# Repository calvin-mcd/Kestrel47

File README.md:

# Kestrel47

collaboration with Falconloft\#4615

40s keyboard inspired by the TG4x. sandwich style case with midlayers case. Supports Bluetooth enabled micro controllers with use of this [power button](https://tech.alpsalpine.com/e/products/detail/SSSS811101/) as well as smd and throughhole style diodes.

Firmware for standard atmega & rp2040 pro micro style controllers is included. Bluetooth is supported for bluemicro style controllers.

concept, case design and firmware by Falconloft\#4615, pcb design by Calvin\#0563

## Layout

[Link](http://www.keyboard-layout-editor.com/#/gists/43b69fae42faf7c21a81fad3a4cf8861)

## Pictures

## Firmware

Firmware for both Atmega and rp2040 controllers is functional and included.

The Bluetooth firmware is zmk based, functional and included.

## Disclaimer

This PCB has been fully tested and confirmed to work. The members of the PCB development team are however not liable if you end up with a non-functional pcb. Order at your own risk. Support will not be provided but pull requests will be reviewed and possibly accepted.

## License

Shield: 

This work is licensed under a  
[Creative Commons Attribution-NonCommercial-ShareAlike 4.0 International License](http://creativecommons.org/licenses/by-nc-sa/4.0/).

## Credits

Any questions, contact Falconloft\#4615 & Calvin\#0563 on Discord.

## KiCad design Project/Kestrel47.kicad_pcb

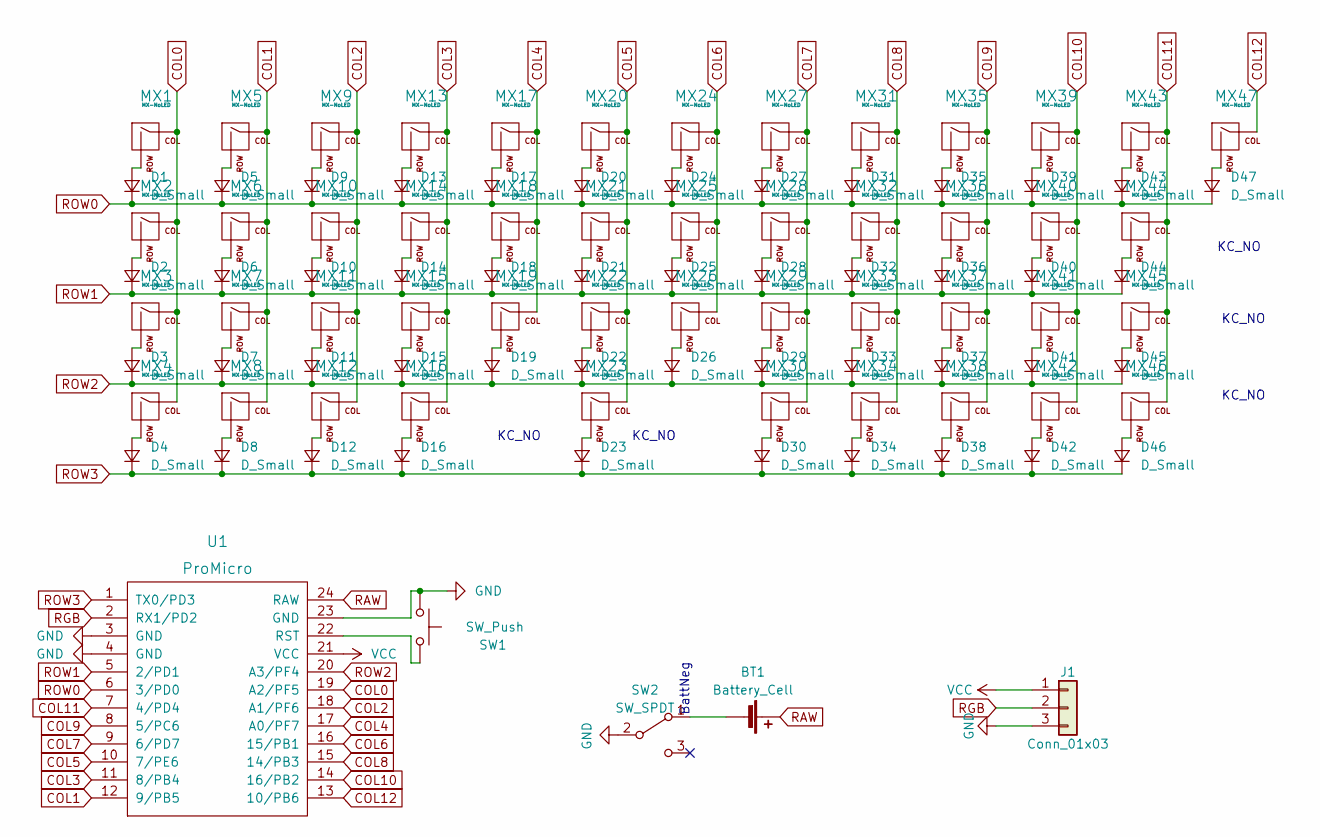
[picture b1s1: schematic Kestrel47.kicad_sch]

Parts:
BT1: Battery_Cell; cell_pads
D1, D2, D3, D4, D5, D6, D7, D8, D9, D10, D11, D12, D13, D14, D15, D16, D17, D18, D19, D20, D21, D22, D23, D24, D25, D26, D27, D28, D29, D30, D31, D32, D33, D34, D35, D36, D37, D38, D39, D40, D41, D42, D43, D44, D45, D46, D47: D_Small; ComboDiode
J1: Conn_01x03; PinSocket_1x03_P2.00mm_Vertical
MX1, MX5, MX6, MX7, MX8, MX9, MX10, MX11, MX12, MX13, MX14, MX15, MX17, MX18, MX19, MX20, MX21, MX22, MX23, MX24, MX25, MX26, MX27, MX28, MX29, MX31, MX32, MX33, MX34, MX35, MX36, MX37, MX38, MX39, MX40, MX41, MX42, MX43, MX47: MX-NoLED; MXOnly-1U-NoLED
MX2, MX46: MX-NoLED; MXOnly-1.25U-NoLED
MX3, MX45: MX-NoLED; MXOnly-1.5U-NoLED
MX4, MX44: MX-NoLED; MXOnly-1.75U-NoLED
MX16, MX30: MX-NoLED; MXOnly-2U-ReversedStabilizers-NoLED
SW1: SW_Push; PinHeader_1x02_P2.54mm_Vertical
SW2: SW_SPDT; switch_SSSS811101
U1: ProMicro; ArduinoProMicro

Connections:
ROW3: D4.1 (K), D8.1 (K), D12.1 (K), D16.1 (K), D23.1 (K), D30.1 (K), D34.1 (K), D38.1 (K), D42.1 (K), D46.1 (K), U1.1 (TX0/PD3)
COL0: MX1.1 (COL), MX2.1 (COL), MX3.1 (COL), MX4.1 (COL), U1.19 (A2/PF5)
COL1: MX5.1 (COL), MX6.1 (COL), MX7.1 (COL), MX8.1 (COL), U1.12 (9/PB5)
COL2: MX9.1 (COL), MX10.1 (COL), MX11.1 (COL), MX12.1 (COL), U1.18 (A1/PF6)
COL3: MX13.1 (COL), MX14.1 (COL), MX15.1 (COL), MX16.1 (COL), U1.11 (8/PB4)
COL4: MX17.1 (COL), MX18.1 (COL), MX19.1 (COL), U1.17 (A0/PF7)
COL5: MX20.1 (COL), MX21.1 (COL), MX22.1 (COL), MX23.1 (COL), U1.10 (7/PE6)
COL6: MX24.1 (COL), MX25.1 (COL), MX26.1 (COL), U1.16 (15/PB1)
COL7: MX27.1 (COL), MX28.1 (COL), MX29.1 (COL), MX30.1 (COL), U1.9 (6/PD7)
COL8: MX31.1 (COL), MX32.1 (COL), MX33.1 (COL), MX34.1 (COL), U1.15 (14/PB3)
COL9: MX35.1 (COL), MX36.1 (COL), MX37.1 (COL), MX38.1 (COL), U1.8 (5/PC6)
COL10: MX39.1 (COL), MX40.1 (COL), MX41.1 (COL), MX42.1 (COL), U1.14 (16/PB2)
COL11: MX43.1 (COL), MX44.1 (COL), MX45.1 (COL), MX46.1 (COL), U1.7 (4/PD4)
COL12: MX47.1 (COL), U1.13 (10/PB6)
GND: J1.3, SW1.1, SW2.2 (B), U1.3 (GND), U1.4 (GND), U1.23 (GND)
unnamed: BT1.2 (-), SW2.1 (A)
unnamed: D1.2 (A), MX1.2 (ROW)
unnamed: D2.2 (A), MX2.2 (ROW)
unnamed: D3.2 (A), MX3.2 (ROW)
unnamed: D4.2 (A), MX4.2 (ROW)
unnamed: D5.2 (A), MX5.2 (ROW)
unnamed: D6.2 (A), MX6.2 (ROW)
unnamed: D7.2 (A), MX7.2 (ROW)
unnamed: D8.2 (A), MX8.2 (ROW)
unnamed: D9.2 (A), MX9.2 (ROW)
unnamed: D10.2 (A), MX10.2 (ROW)
unnamed: D11.2 (A), MX11.2 (ROW)
unnamed: D12.2 (A), MX12.2 (ROW)
unnamed: D13.2 (A), MX13.2 (ROW)
unnamed: D14.2 (A), MX14.2 (ROW)
unnamed: D15.2 (A), MX15.2 (ROW)
unnamed: D16.2 (A), MX16.2 (ROW)
unnamed: D17.2 (A), MX17.2 (ROW)
unnamed: D18.2 (A), MX18.2 (ROW)
unnamed: D19.2 (A), MX19.2 (ROW)
unnamed: D20.2 (A), MX20.2 (ROW)
unnamed: D21.2 (A), MX21.2 (ROW)
unnamed: D22.2 (A), MX22.2 (ROW)
unnamed: D23.2 (A), MX23.2 (ROW)
unnamed: D24.2 (A), MX24.2 (ROW)
unnamed: D25.2 (A), MX25.2 (ROW)
unnamed: D26.2 (A), MX26.2 (ROW)
unnamed: D27.2 (A), MX27.2 (ROW)
unnamed: D28.2 (A), MX28.2 (ROW)
unnamed: D29.2 (A), MX29.2 (ROW)
unnamed: D30.2 (A), MX30.2 (ROW)
unnamed: D31.2 (A), MX31.2 (ROW)
unnamed: D32.2 (A), MX32.2 (ROW)
unnamed: D33.2 (A), MX33.2 (ROW)
unnamed: D34.2 (A), MX34.2 (ROW)
unnamed: D35.2 (A), MX35.2 (ROW)
unnamed: D36.2 (A), MX36.2 (ROW)
unnamed: D37.2 (A), MX37.2 (ROW)
unnamed: D38.2 (A), MX38.2 (ROW)
unnamed: D39.2 (A), MX39.2 (ROW)
unnamed: D40.2 (A), MX40.2 (ROW)
unnamed: D41.2 (A), MX41.2 (ROW)
unnamed: D42.2 (A), MX42.2 (ROW)
unnamed: D43.2 (A), MX43.2 (ROW)
unnamed: D44.2 (A), MX44.2 (ROW)
unnamed: D45.2 (A), MX45.2 (ROW)
unnamed: D46.2 (A), MX46.2 (ROW)
unnamed: D47.2 (A), MX47.2 (ROW)
unnamed: SW1.2, U1.22 (RST)
RAW: BT1.1 (+), U1.24 (RAW)
RGB: J1.2, U1.2 (RX1/PD2)
ROW0: D1.1 (K), D5.1 (K), D9.1 (K), D13.1 (K), D17.1 (K), D20.1 (K), D24.1 (K), D27.1 (K), D31.1 (K), D35.1 (K), D39.1 (K), D43.1 (K), D47.1 (K), U1.6 (3/PD0)
ROW1: D2.1 (K), D6.1 (K), D10.1 (K), D14.1 (K), D18.1 (K), D21.1 (K), D25.1 (K), D28.1 (K), D32.1 (K), D36.1 (K), D40.1 (K), D44.1 (K), U1.5 (2/PD1)
ROW2: D3.1 (K), D7.1 (K), D11.1 (K), D15.1 (K), D19.1 (K), D22.1 (K), D26.1 (K), D29.1 (K), D33.1 (K), D37.1 (K), D41.1 (K), D45.1 (K), U1.20 (A3/PF4)
VCC: J1.1, U1.21 (VCC)

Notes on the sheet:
KC_NO
BattNeg

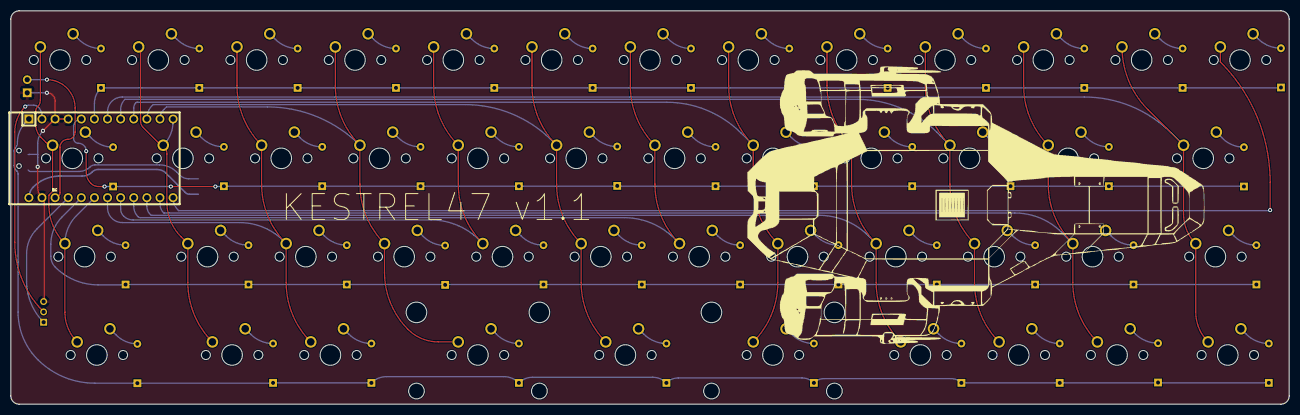
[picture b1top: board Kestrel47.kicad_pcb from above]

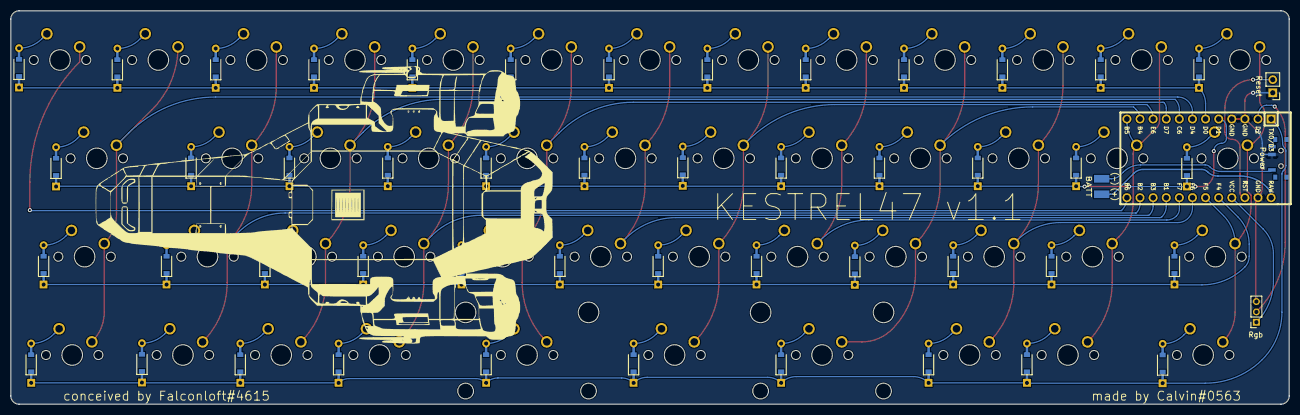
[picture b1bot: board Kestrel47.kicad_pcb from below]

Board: 2 copper layers, 247.6 x 76.2 mm, 99 parts (5 on the bottom side), 70 nets.

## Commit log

2022-12-16 initialised project
2022-12-17 clean up
2022-12-22 rerouting mistake, adding rgb and power button
2022-12-22 edits
2022-12-27 cleaned up power routing
2022-12-31 silkscreen update
2023-01-10 work on readme, added case files
2023-01-10 added license non-commercial
2023-01-15 backup
2023-02-06 added pictures, and edited readme
2023-02-06 added diodes
    still missing blurp about switch
2023-02-06 finialising readme, added firmware
2023-02-06 firmware blurb added to readme
2023-02-17 back-ups
2023-04-07 different firmware
2023-04-22 atmega firmware added
2023-06-21 BLE firmware added
2023-08-29 removed old BLE firmware, added zmk based firmware
